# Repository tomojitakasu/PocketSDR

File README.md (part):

# **Pocket SDR - An Open-Source GNSS SDR,<br> ver. 0.22**

<div style="text-align: right;">
<strong>2026-11-03</strong>
</div>

---

## **Overview**

**Pocket SDR** is an open-source Global Navigation Satellite System (GNSS) receiver based
on software-defined radio (SDR) technology. It consists of RF frontend devices named
**Pocket SDR FE**, utilities for these devices, and GNSS SDR applications (APs) written
in Python, C, and C++. It supports almost all signals for **GPS**, **GLONASS**, **Galileo**,
**QZSS**, **BeiDou**, **NavIC**, and **SBAS**.

The Pocket SDR FE device includes 2, 4, or 8 RF frontend channels, supporting the
GNSS L1 band (1525 - 1610 MHz) or L2/L5/L6 bands (1160 - 1290 MHz). For these signal bands, refer to [**GNSS Signal Bands**](https://github.com/tomojitakasu/PocketSDR/blob/master/doc/signal_bands.pdf). Each RF channel
of the Pocket SDR FE device provides IF (intermediate-frequency) bandwidth of up to 36 MHz. The ADC sampling rate can be configured up to 32 Msps (FE 2CH) or 48 Msps (FE 4CH and FE 8CH).

Pocket SDR also includes utility programs to configure the Pocket SDR FE devices,
capture, and dump digitized IF data.
Additionally, Pocket SDR provides GNSS SDR APs to display the PSD (power spectrum density) of captured IF data, search for GNSS signals, track these signals, decode navigation data, and generate PVT (position, velocity, and time) solutions.
These utilities and APs are compatible with **Windows**, **Linux**, **Raspberry Pi OS**, **macOS**, and other environments.

The supported GNSS signals by Pocket SDR are as follows. For details on these signals and Pocket SDR signal IDs, refer to
[**GNSS Signals**](https://github.com/tomojitakasu/PocketSDR/blob/master/doc/signal_IDs.pdf).

* **GPS**: L1C/A, L1C-D, L1C-P, L2C-M, L5-I, L5-Q
* **GLONASS**: L1C/A (L1OF), L2C/A (L2OF), L1OCd, L1OCp, L2OCp, L3OCd, L3OCp
* **Galileo**: E1-B, E1-C, E5a-I, E5a-Q, E5b-I, E5b-Q, E5AltBOC (E5abQ), E6-B, E6-C
* **QZSS**: L1C/A, L1C/B, L1C-D, L1C-P, L1S, L2C-M, L5-I, L5-Q, L5S-I, L5S-Q, L6D, L6E
* **BeiDou**: B1I, B1C-D, B1C-P, B2a-D, B2a-P, B2I, B2b-I, B3I
* **NavIC**: L1-SPS-D, L1-SPS-P, L5-SPS
* **SBAS**: L1C/A, L5-I, L5-Q

These utilities and APs are written in Python, C, and C++ in a compact and modular way,
making them easy to modify for adding custom algorithms.

In addition to the Pocket SDR FE devices, Pocket SDR supports third-party
SDR hardware (**USRP**, **LimeSDR**, **bladRF**, **PlutoSDR**, **RTL-SDR**, and so on) via 
[**SoapySDR**](https://github.com/pothosware/SoapySDR/wiki).
See [**SoapySDR Device Notes**](https://github.com/tomojitakasu/PocketSDR/blob/master/doc/notes_soapy_dev.md) for verified devices,
installation notes, and device-specific caveats.

<p align="center">
  
  <b>Pocket SDR FE 2CH (v.2.0 and v.2.3), FE 4CH</b>
</p>

<p align="center">
  
  <b>Pocket SDR FE 8CH (2-RF-inputs and 8-RF-inputs)</b>
</p>

<p align="center">
  
  <b>GUI-based Real-Time GNSS SDR Receiver AP</b>
</p>

--------------------------------------------------------------------------------
<div class="pagebreak"></div>

## **Documents**

- Pocket SDR C Library API Reference
(https://github.com/tomojitakasu/PocketSDR/tree/master/doc/api_ref.pdf)

- Pocket SDR Command Reference
(https://github.com/tomojitakasu/PocketSDR/tree/master/doc/command_ref.pdf)

- Pocket SDR GNSS SDR Algorithm Description
(https://github.com/tomojitakasu/PocketSDR/tree/master/doc/algo_desc.pdf)

- Pocket SDR GNSS SDR アルゴリズム解説
(https://github.com/tomojitakasu/PocketSDR/tree/master/doc/algo_desc_jp.pdf)

- T.Takasu, An Open Source GNSS SDR: Development and Application, IPNTJ Next GNSS
Technology WG, February 21, 2022
(https://gpspp.sakura.ne.jp/paper2005/IPNTJ_NEXTWG_202202.pdf)

- T.Takasu, Development of QZSS L6 Receiver without Pilot Signal by using SDR,
IPNTJ Annual Conference, June 10, 2022
(https://gpspp.sakura.ne.jp/paper2005/IPNTJ_20220610.pdf)

- T.Takasu, Pocket SDR: Design, Implementation and Applications, A seminar for
GNSS Software Defined Receivers, Nov 19, 2024
(https://gpspp.sakura.ne.jp/paper2005/pocketsdr_seminar_202411_revA.pdf)

--------------------------------------------------------------------------------
<div class="pagebreak"></div>

## **Directory Structure and Contents**
```
PocketSDR
├── bin         # Pocket SDR APs binary programs
├── app         # Pocket SDR APs source programs
│   ├── pocket_conf  # Pocket SDR FE device configurator
│   ├── pocket_dump  # Dump digital IF data of Pocket SDR FE device
│   ├── pocket_scan  # Scan and list USB devices
│   ├── pocket_acq   # GNSS signal acquisition
│   ├── pocket_trk   # GNSS signal tracking and PVT generation
│   ├── pocket_web   # GNSS receiver server with Web UI
│   ├── pocket_snap  # Snapshot Positioning
│   ├── pocket_calib # Antenna array attitude / per-CH bias calibration
│   ├── convbin      # RINEX converter supporting Pocket SDR
│   └── str2str      # Stream converter (RTKLIB-derived)
├── src         # Pocket SDR library source programs
├── html        # Web UI files served by pocket_web (JS + CSS, no build step)
├── python      # Pocket SDR Python scripts (incl. pocket_sdr.py GUI)
├── lib         # Libraries for APs and Python scripts
│   ├── win32        # Built libraries for Windows (UCRT64)
│   ├── macos        # Built libraries for macOS
│   ├── linux        # Built libraries for Linux or Raspberry Pi OS
│   ├── build        # Makefiles to build libraries (UCRT64 / Linux / macOS)
│   ├── cyusb        # Cypress EZ-USB API (CyAPI.a) and includes
│   ├── RTKLIB       # RTKLIB source programs based on 2.4.3 b34
│   ├── pocketfft    # PocketFFT (header-only FFT, used internally)
│   └── SoapySDR     # SoapySDR headers + import lib for SDR device support
├── conf        # Configuration files for Pocket SDR FE
├── FE_2CH      # Pocket SDR FE 2CH H/W and F/W
├── FE_4CH      # Pocket SDR FE 4CH H/W and F/W
├── FE_8CH      # Pocket SDR FE 8CH H/W and F/W (3-bit RF samples)
├── driver      # Driver installation instruction for Pocket SDR FE
├── doc         # Documents (incl. api_ref.md, command_ref.md)
├── image       # Image files for documents
├── sample      # Sample digital IF data captured by Pocket SDR FE
└── test        # Test codes, scripts and data
    ├── python       # Python scripts for tests
    ├── script       # Shell scripts for tests
    ├── src          # source programs for tests
    └── utest        # makefile for unit tests

```
--------------------------------------------------------------------------------
<div class="pagebreak"></div>

## **Installation for Windows**

* Download and extract PocketSDR.zip or clone the git repository [**here**](https://github.com/tomojitakasu/PocketSDR) to an appropriate directory <install_dir>.
to an appropriate directory <install_dir>.
```
> unzip PocketSDR.zip
or
> git clone https://github.com/tomojitakasu/PocketSDR
```
* Install USB device driver for Pocket SDR FE according to [**driver/readme.txt**](https://github.com/tomojitakasu/PocketSDR/blob/master/driver/readme.txt)
.
* Install [**Python**](https://www.python.org/) with checking "Add python.exe to PATH".
* Install additional python packages as follows.
```
> pip install numpy scipy matplotlib
```
* (Optional) To use SoapySDR-supported devices (LimeSDR, HackRF, RTL-SDR,
  bladeRF, etc.), install [**radioconda**](https://github.com/ryanvolz/radioconda)
  and add `<radioconda_install_dir>\Library\bin` to PATH. See
  [SoapySDR Device Notes](https://github.com/tomojitakasu/PocketSDR/blob/master/doc/notes_soapy_dev.md#windows) for per-device
  packages, Zadig driver setup, and bladeRF version caveats.
* Add the Pocket SDR binary programs path (<install_dir>\PocketSDR\bin) to 
  the command search path (Path) of Windows environment variables.
* Add the Pocket SDR Python scripts path (<install_dir>\PocketSDR\python) to 
  the command search path (Path) of Windows environment variables.

--------------------------------------------------------------------------------

## **To rebuild binary programs for Windows**
* If you want to rebuild the binary utilities, APs, or shared libraries for the python APs
for Windows, you need [**MSYS2**](https://www.msys2.org/) with the **UCRT64** environment.
The UCRT64 toolchain links against the same C runtime (`ucrtbase.dll`) as
[**radioconda**](https://github.com/ryanvolz/radioconda)'s SoapySDR DLLs, which
gives stable high-rate streaming with SDR hardware (e.g., LimeSDR at 64 Msps).
The legacy **MINGW64** environment also builds, but suffers significant
performance loss with SoapySDR devices due to msvcrt/UCRT mixing.

* Open the **MSYS2 UCRT64** shell and install the development tools and the
  Python stack used by the python APs:
```
$ pacman -Syy
$ pacman -S git make
$ pacman -S mingw-w64-ucrt-x86_64-gcc
$ pacman -S mingw-w64-ucrt-x86_64-binutils
$ pacman -S mingw-w64-ucrt-x86_64-python
$ pacman -S mingw-w64-ucrt-x86_64-python-numpy
$ pacman -S mingw-w64-ucrt-x86_64-python-scipy
$ pacman -S mingw-w64-ucrt-x86_64-python-matplotlib
```
* If you intend to use SoapySDR-supported devices, install radioconda first.
  The default radioconda location used by the Makefiles is
  `/c/Users/<user>/radioconda/Library`. If installed elsewhere, override
  with `SOAPY_ROOT` on the make command line. See
  [SoapySDR Device Notes](https://github.com/tomojitakasu/PocketSDR/blob/master/doc/notes_soapy_dev.md#windows-build-notes)
  for details.

* If SoapySDR device support is not required, build `libsdr`, `pocket_trk`,
  and `pocket_dump` with `USE_SOAPY=0`. Pocket SDR FE USB devices and
  IF-file based processing still work; only SoapySDR device input is
  disabled. If you are rebuilding an existing tree, run `make clean` first.
```
$ cd <install_dir>/lib/build
$ make clean && make USE_SOAPY=0 && make install
$ cd <install_dir>/app/pocket_trk
$ make clean && make USE_SOAPY=0 && make install
$ cd <install_dir>/app/pocket_dump
$ make clean && make USE_SOAPY=0 && make install
```

* Move to the library build directory and build libraries.
```
$ cd <install_dir>/lib/build
$ make
$ make install
```
  The default radioconda location is `/c/Users/<user>/radioconda/Library`. If
  installed elsewhere, override on the command line:
```
$ make SOAPY_ROOT=/c/path/to/radioconda/Library
```

* Move to the application program directory and build utilities and APs.
```
$ cd <install_dir>/app
$ make
$ make install
```

* To run unit tests for the libraries:
```
$ cd <install_dir>/test/utest
$ make
$ make test
==> test_sdr_array.exe
test_sdr_array_new_free_api ... OK
test_sdr_array_ant_pos_api ... OK
t...
test_sdr_usb_req_control ... OK
```

--------------------------------------------------------------------------------
<div class="pagebreak"></div>

## **Installation for Linux or Raspberry Pi OS**

> **Note**: Pocket SDR has been verified on Ubuntu / Debian-based Linux
> distributions and on **Raspberry Pi OS (Bookworm) on Raspberry Pi 5**
> (aarch64). The Pi 5 has been confirmed to handle Pocket SDR FE and the
> apt-installed SoapySDR devices for typical L1 / L2 single-channel use;
> see the **Notes for Raspberry Pi 5** subsection below for hardware
> caveats (USB power, USB 3.0 routing, CPU limits).

* You need fundamental development packages and some libraries. Confirm the following
packages installed: git, gcc, g++, make, libusb-1.0-0-dev, libfftw3-dev, python3, python3-numpy,
python3-scipy, python3-matplotlib, python3-tk
* (Optional) To use SoapySDR-supported devices (LimeSDR, HackRF, RTL-SDR,
  SDRPlay, bladeRF, etc.), install SoapySDR and the per-device modules:
```
$ sudo apt install libsoapysdr-dev soapysdr-tools soapysdr-module-all
```
  See [SoapySDR Device Notes](https://github.com/tomojitakasu/PocketSDR/blob/master/doc/notes_soapy_dev.md#linux--raspberry-pi-os)
  for per-device package names, udev access, UHD image installation, and
  the Ubuntu 24.04 bladeRF module update workaround.

* Download and extract PocketSDR.zip or clone the git repository to an appropriate directory <install_dir>.
```
$ unzip PocketSDR.zip
or
$ git clone https://github.com/tomojitakasu/PocketSDR
```
* Move to the library build directory and build libraries.
```
$ cd <install_dir>/lib/build
$ make
$ make install
```
* Move to the application program directory and build utilities and APs.
```
$ cd <install_dir>/app
$ make
$ make install
```
* Add the Pocket SDR binary programs path (<install_dir>/PocketSDR/bin) to the command search path.

* (Recommended) Install the udev rule so the Pocket SDR FE device is
  accessible to a normal user account (no `sudo` required). The repository
  ships a ready-to-use rule at [`driver/99-pocket-sdr.rules`](https://github.com/tomojitakasu/PocketSDR/blob/master/driver/99-pocket-sdr.rules) that grants the
  `plugdev` group read/write access to Pocket SDR FE 2CH (Cypress
  EZ-USB FX2LP, VID `04B4` / PID `1004`) and FE 4CH / 8CH (Cypress
  EZ-USB FX3, VID `04B4` / PID `00F1`):
```
$ sudo cp <install_dir>/driver/99-pocket-sdr.rules /etc/udev/rules.d/
$ sudo udevadm control --reload-rules && sudo udevadm trigger
$ sudo usermod -aG plugdev $USER     # add yourself to plugdev
```
  Log out and back in (or reboot) so the new group membership takes effect,
  then unplug and re-plug the device. After that, `pocket_scan`,
  `pocket_conf`, `pocket_dump`, `pocket_trk`, and `pocket_sdr.py` all run
  without `sudo`.

  Verify the rule is in effect:
```
$ lsusb -d 04b4:                         # confirm the device is enumerated
$ ls -l /dev/bus/usb/<bus>/<dev>          # group should be "plugdev", mode 0660
$ pocket_scan                             # should list the device
```
  If your distribution uses a different group than `plugdev` (e.g.
  `dialout` on some systems, or systemd-logind's `uaccess` is sufficient
  on its own), adjust `GROUP=` in the rule file or rely on the
  `TAG+="uaccess"` line which grants access to the currently logged-in
  seat user on systemd-based systems.

* If you skip the udev rule, you must run the Pocket SDR utilities under
  `sudo` to access the USB device:
```
$ sudo pocket_conf ../conf/pocket_L1L6_12MHz.conf
$ sudo pocket_dump -t 10 ch1.bin ch2.bin
$ sudo pocket_sdr.py
```

### **Notes for Raspberry Pi 5**

Raspberry Pi 5 (Cortex-A76 4-core @ 2.4 GHz, aarch64) runs the same
build path as desktop Linux above. The Makefiles auto-detect aarch64
and enable NEON SIMD optimizations (`-DNEON`). A few Pi-specific
constraints to be aware of:

* **USB power budget**: Pi 5 advertises 5V / 5A on the official PSU but
  the USB ports share a ~1.6 A budget. USRP B210 (~2 A peak), Pocket
  SDR FE 8CH, and BladeRF 2.0 typically need either a USB Y-cable
  (separate +5V feed) or a **self-powered (externally-fed) USB hub**.
  Symptoms of insufficient power are intermittent USB resets, FPGA
  bitstream upload failures (USRP), and dropped samples.

* **USB 3.0 routing**: Pi 5 has 2× USB 3.0 + 2× USB 2.0 ports. Always
  connect high-rate SDRs (LimeSDR, USRP B210, Pocket SDR FE 8CH) to a
  USB 3.0 port. Verify enumeration speed with:
```
$ lsusb -t
```
  The relevant device should show `5000M` (USB 3.0) ? `480M` means the
  device fell back to USB 2.0, which is bandwidth-limited and will drop
  samples at high rates.

* **CPU / sample rate limits**: Pi 5 holds up well thanks to NEON SIMD
  acceleration. Measured load (`pocket_trk` realtime, single-band L1
  tracking, all-in-view PRNs):

  | Device | Sample rate × tracked channels | CPU load (of 400% = 4 cores) |
  |---|---|---|
  | LimeSDR USB | 32 Msps × 7 ch | ~280% |
  | USRP B210 | 32 Msps × 8 ch | ~290% |
  | PlutoSDR | 6 Msps × 10 ch | ~121% |
  | RTL-SDR | 2.4 Msps × 16 ch | ~102% |

  32 Msps with many tracked channels is workable but leaves limited
  headroom for additional bands or PVT processing. **8 Msps** is a
  comfortable sweet spot for general L1 use on Pi 5. Heavier configs
  (LimeSDR 60 Msps × 2-band, Pocket SDR FE 8CH × multi-band) will
  saturate the Pi 5 CPU and are intended for desktop use.

* **PocketFFT vs FFTW3**: PocketFFT (default) works on aarch64 with
  NEON. If FFT becomes a bottleneck for your workload, FFTW3 is
  marginally faster on large transforms ? install with
  `sudo apt install libfftw3-dev` and switch the build per the
  [Using FFTW3 instead of PocketFFT](#using-fftw3-instead-of-pocketfft-optional)
  section below.

* **Storage**: For long IF data captures (`pocket_dump -t <long>`,
  `pocket_trk -raw`), use a USB 3.0 SSD or NVMe HAT. The microSD card
  on stock Pi 5 cannot sustain >50 MB/s writes for extended periods
  and will drop samples.

--------------------------------------------------------------------------------
<div class="pagebreak"></div>

## **Installation for macOS**

> **Note**: Verified on Apple Silicon (arm64). Pocket SDR FE 2/4/8CH (USB)
> has been confirmed working. For SoapySDR devices on macOS, see
> [SoapySDR Device Notes](https://github.com/tomojitakasu/PocketSDR/blob/master/doc/notes_soapy_dev.md#macos).

* You need [**Homebrew**](https://brew.sh) as a base package manager. Install
  Homebrew by following the instructions on its site, then install
  development tools:
```
$ brew install libusb fftw
```

* (Optional) Install [**radioconda**](https://github.com/ryanvolz/radioconda)
  to use SoapySDR devices and a self-contained Python environment:
```
$ curl -L -O https://github.com/ryanvolz/radioconda/releases/latest/download/Radioconda-MacOSX-arm64.sh
$ bash Radioconda-MacOSX-arm64.sh
```
  For Intel mac use `Radioconda-MacOSX-x86_64.sh`. Known macOS SoapySDR
  packaging workarounds are collected in
  [SoapySDR Device Notes](https://github.com/tomojitakasu/PocketSDR/blob/master/doc/notes_soapy_dev.md#macos).

* Download and extract PocketSDR.zip or clone the git repository to an
  appropriate directory <install_dir>.
```
$ unzip PocketSDR.zip
or
$ git clone https://github.com/tomojitakasu/PocketSDR
```
* Build libraries and applications. The Makefiles auto-detect Apple
  Silicon (`Darwin arm64`) and use `clang++` for C++ sources and pull
  Homebrew's `libusb` / `fftw` headers from `/opt/homebrew/include`:
```
$ cd <install_dir>/lib/build
$ make
$ make install
$ cd <install_dir>/app
$ make
$ make install
```
* Add `<install_dir>/PocketSDR/bin` to the command search path.

* For SoapySDR-supported devices, use the driver shortcuts in
  `<install_dir>/app/pocket_trk/pocket_trk.sh`. See
  [SoapySDR Device Notes](https://github.com/tomojitakasu/PocketSDR/blob/master/doc/notes_soapy_dev.md#runtime-driver-shortcuts).

* Pocket SDR FE 2CH / 4CH / 8CH USB devices work on macOS via libusb-1.0
  with **no driver install needed** (Apple's IOUSB stack provides
  raw USB access through libusb). Plug in the device and run:
```
$ pocket_scan                                          # device should be listed
$ pocket_conf <install_dir>/conf/pocket_L1L6_12MHz.conf
$ pocket_dump -t 10 ch1.bin ch2.bin
```

--------------------------------------------------------------------------------
<div class="pagebreak"></div>

## **Using FFTW3 instead of PocketFFT (optional)**

Starting from version 0.15b, Pocket SDR ships with [**PocketFFT**](https://gitlab.mpcdf.mpg.de/mtr/pocketfft) (BSD-3-Clause) as the default FFT backend, replacing [**FFTW3**](https://www.fftw.org/) (GPL). The change is licensing-driven; for most workloads PocketFFT is competitive, but FFTW3 is still slightly faster on large transforms and supports runtime wisdom (auto-tuned plans) ? `pocket_trk` / `pocket_snap` / `pocket_acq` can read `python/fftw_wisdom.txt` for further speed-up.

To build with FFTW3 instead, install the library and build `libsdr` and the
FFT-using applications with `USE_FFTW=1`.

* Install FFTW3 (single-precision):
```
$ pacman -S mingw-w64-ucrt-x86_64-fftw    # MSYS2 UCRT64 (Windows)
$ sudo apt install libfftw3-dev           # Ubuntu / Debian / Raspberry Pi OS
$ brew install fftw                       # macOS
```
* Rebuild from scratch:
```
$ cd <install_dir>/lib/build
$ make clean && make USE_FFTW=1 && make USE_FFTW=1 install
$ cd <install_dir>/app/pocket_acq
$ make clean && make USE_FFTW=1 && make install
$ cd <install_dir>/app/pocket_snap
$ make clean && make USE_FFTW=1 && make install
$ cd <install_dir>/app/pocket_calib
$ make clean && make USE_FFTW=1 && make install
$ cd <install_dir>/app/pocket_dump
$ make clean && make USE_FFTW=1 && make install
$ cd <install_dir>/app/pocket_trk
$ make clean && make USE_FFTW=1 && make install
```
* (Optional, FFTW3 only) Generate a wisdom file tuned for the host CPU. Once present, `pocket_trk`, `pocket_snap`, and `pocket_acq` pick it up automatically.
```
$ cd <install_dir>/app/pocket_trk
$ ./fftw_wisdom -n 4096
$ cp fftw_wisdom.txt ../../python/
```

Note: FFTW3 is GPL-licensed, so a binary linked against it inherits GPL terms. Keep this in mind when redistributing.

--------------------------------------------------------------------------------
<div class="pagebreak"></div>

## **Using AVX-512 instructions (optional)**

On x86-64 CPUs with AVX-512 (AMD Zen 4 or later such as Ryzen 9000 series,
Intel Ice Lake or later), `libsdr` can be built with `USE_AVX512=1` to use the
AVX-512 versions of the carrier mixer, correlator, LPF and array covariance
kernels (`-DAVX512`) instead of the default AVX2 ones. The APs link `libsdr`
statically, so rebuild them after the library. A binary built with
`USE_AVX512=1` does not run on a CPU without AVX-512.
```
$ cd <install_dir>/lib/build
$ make clean && make USE_AVX512=1 && make install
$ cd <install_dir>/app
$ make clean && make && make install
```
The unit tests can be built with the same option: `make -C test/utest USE_AVX512=1`.

--------------------------------------------------------------------------------
<div class="pagebreak"></div>

## **GNSS SDR Utilities and APs**

Pocket SDR includes the following utilities for the Pocket SDR FE.

- **pocket_scan**: Scans and lists USB Devices.
- **pocket_conf**: Configures Pocket SDR FE device.
- **pocket_dump**: Captures and dumps IF data from the Pocket SDR FE device

Pocket SDR also provides the following GNSS SDR APs:

- **pocket_psd.py** : Plots PSD and histograms of IF data.
- **pocket_acq.py** : Performs GNSS signal acquisition from IF data.
- **pocket_trk.py** : Tracks GNSS signals and decodes navigation data in IF data.
- **pocket_snap.py**: Executes snapshot positioning using captured IF data.
- **pocket_sdr.py** : A GUI-based GNSS SDR receiver application.
- **pocket_plot.py**: Plots receiver logs generated by pocket_trk or pocket_sdr.py.
- **pocket_acq**    : A C-version of pocket_acq.py (w/o graphical plots).
- **pocket_trk**    : A C-version of pocket_trk.py (w/o graphical plots).
- **pocket_snap**   : A C-version of pocket_snap.py.
- **pocket_web**    : A GNSS SDR receiver server controlled from a Web UI.

For more details about these utilities and APs, please refer to [**Pocket SDR Command References**](https://github.com/tomojitakasu/PocketSDR/blob/master/doc/command_ref.pdf).

--------------------------------------------------------------------------------

## **GUI-based Real-Time GNSS SDR Receiver AP**

Starting from version 0.13, Pocket SDR includes a GUI-based real-time GNSS SDR
receiver AP, **pocket_sdr.py**. To execute the application, follow these steps:

```
$ chmod +x <install_dir>/python/pocket_sdr.py
$ sudo ./<install_dir>/python/pocket_sdr.py
or alternatively:
$ sudo python <install_dir>/python/pocket_sdr.py
```

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
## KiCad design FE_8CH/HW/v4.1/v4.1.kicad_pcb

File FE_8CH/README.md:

# **Pocket SDR FE 8CH - An Open-Source GNSS SDR RF Frontend**

## **Overview**

Pocket SDR FE 8H is an open-source GNSS SDR RF frontend device for Pocket SDR.
The device consists of 8 CH Maxim MAX2771 ([1]) GNSS RF front-end ICs (LNA, mixer,
filter, ADC, frequency synthesizer) and a Cypress EZ-USB FX3 USB 3.0 controller
([2], [3], [4]) to connect to host PCs. All the RF CHs are able to be configured for
GNSS L1 band (1525 - 1610 MHz), or GNSS L2/L5/L6 band (1160 - 1290 MHz).
The frequency of the reference oscillator (TCXO) is 24.000 MHz, and the ADC
sampling rate can be configured up to 48 Msps.

--------------------------------------------------------------------------------

## **Specifications**

* **Number of RF Inputs**: 8 CH or 2 CH
* **Number of RF Channels**: 8 CH
* **LO (PLL) Frequency**: 1525 ~ 1610 MHz (GNSS L1 band) or
                      1160 ~ 1290 MHz (GNSS L2/L5/L6 band)
* **IF Bandwidth**: 2.5 ~ 36 MHz
* **Sampling Rate**: 4, 6, 8, 12, 16, 24, 32 or 48 Msps
* **Sampling Type**: I-sampling 2 or 3 bits,  I/Q-sampling 2 bits
* **Host I/F**: USB 3.0 (USB 3.2 Gen1, super-speed 5Gbps), type-C
* **Power Supply**: 5V 330 mA, USB bus power

--------------------------------------------------------------------------------

## **Directory Structure and Contents**
```
FE_8CH  -+-- HW     Pocket SDR FE 8CH hardware design data
         |   |
         |   +-- v4.0     Pocket SDR FE 8CH PCB H/W data
         |   |   +-- v4.0.kicad.*     KiCAD PCB and circuit design data
         |   |   +-- v4.0.pretty      KiCAD module data
         |   |   +-- v4.0_gerber.zip  gerber data ZIP file
         |   |   +-- v4.0_gerber      gerber data
         |   |   +-- v4.0_parts.xlsx  BOM (parts list) Excel data
         |   |   +-- pocket_sdr_v2.3-eagle-import.kicad_sym  KiCAD symbol data
         |   |   +-- v4.0_case.f3d    Pocket SDR FE 8CH case Autodesk Fusion data
         |   |   +-- v4.0_case_panel_f.f3d frontpanel Autodesk Fusion data
         |   |   +-- v4.0_case_panel_b.f3d backpanel Autodesk Fusion data
         |   |   +-- ...
         |   +-- v4.1     Pocket SDR FE 8CH-2ANT PCB H/W data
         |   |   +-- ...
         |   +-- div_4px2 4PX2 RF Divider H/W data
         |       +-- ...
         +-- FW     Pocket SDR FE 8CH firmware
             +-- Packages  Cypress EZ USB Suite files
             +-- v4.0
                 +-- .metadata  Cypress EZ USB Suite files
                 +-- pocket_fw_v4
                     +-- pocket_fw_v4.c  Pocket SDR FE 8CH F/W source
                     +-- pocket_usb_dscr.c USB descriptors source
                     +-- gpif_conf.cyfx  GPIF II Designer config file 
                     +-- gpif_conf.h     GPIF II Designer generated header file
                     +-- ...
                     +-- Release
                         +-- pocket_Fw_v4.img Binary image of the F/W
                         +-- ...
```
--------------------------------------------------------------------------------

## **Rebuild F/W and Write F/W Image to Pocket SDR FE 8CH**

* Install Cypress EZ-USB FX3 Development Kit (ref [5]) to a Windows PC. As default,
it is installed to C:\Program Files (x86)\Cypress\EZ-USB FX3 SDK.
* Execute EZ USB Suite (EZ-USB FX3 SDK\1.3\Eclipse\ezUsbSuite.exe).
* Execute Menu File - Switch Workspace - Others, select <install_dir>\PocketSDR\FE_8CH\FW\v4.0
and open the workspace.
* Select pocket_fw_v4 in Project Explorer and execute Menu Project - Build All and
you can get a F/W image <install_dir>\PocketSDR\FE_8CH\FW/v4.0\pocket_fw_v4\Release\pocket_fw_v4.img.
* Disable EEPROM by connecting the J2 jumper pins on the Pocket SDR FE 8CH PCB and
attach the Pocket SDR FE 8CH via USB cable to the PC.
* Execute USB Control Center (EZ-USB FX3 SDK\1.3\bin\CyControl.exe).
* You can see "Cypress FX3 USB BootLoader Device".
* Re-enable EEPROM by disconnecting the J2 jumper pins on the Pocket SDR FE 8CH PCB.
* In USB Control Center, select "Cypress FX3 USB Bootloader Device", execute menu
Program - FX3 - I2C EEPROM, select the F/W image <install_dir>\PocketSDR\FE_8CH\FW\v4.0\pocket_fw_v4\Release\pocket_fw_v4.img
and open it.
* If you see "Programming succeeded." in status bar, the F/W is properly written
to the PocketSDR FE 8CH.

--------------------------------------------------------------------------------

## **References**

[1] Maxim integrated, MAX2771 Multiband Universal GNSS Receiver, July 2018

[2] Infineon, CYUSB301X, CYUSB201X, EZ-USB FX3 SuperSpeed USB Controller Datasheet,
Rev. Z, September 29, 2022

[3] Cypress Semiconductor, EZ-USB FX3 Technical Reference Manual, Rev.F, May 9, 2019

[4] Cypress Semiconductor, FX3 Programmers Manual, Rev.K

[5] Infineon, EZ-USB FX3 Software Development Kit
    (https://www.infineon.com/cms/jp/design-support/tools/sdk/usb-controllers-sdk/ez-usb-fx3-software-development-kit/)

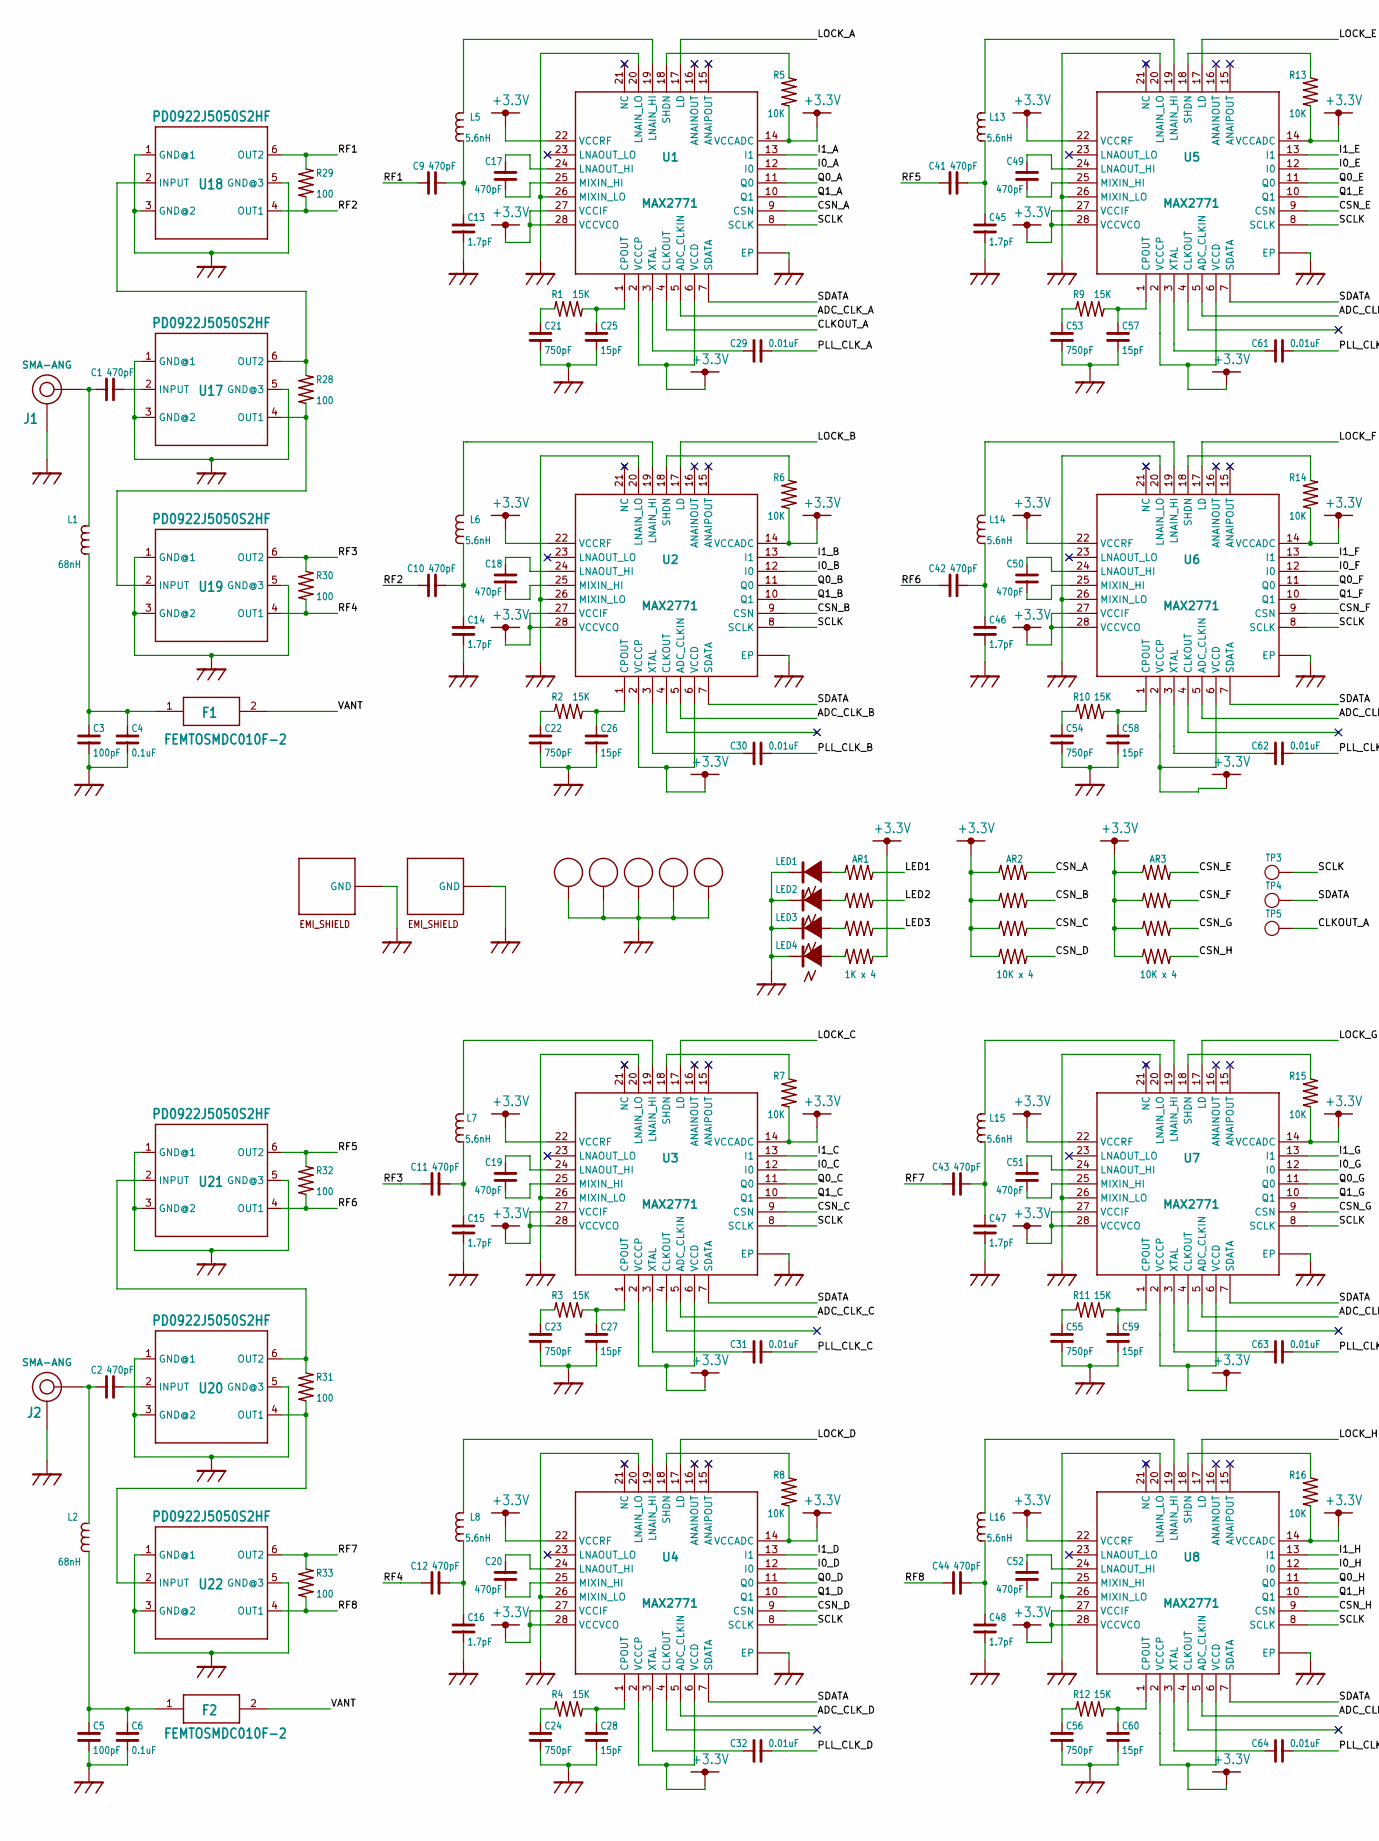
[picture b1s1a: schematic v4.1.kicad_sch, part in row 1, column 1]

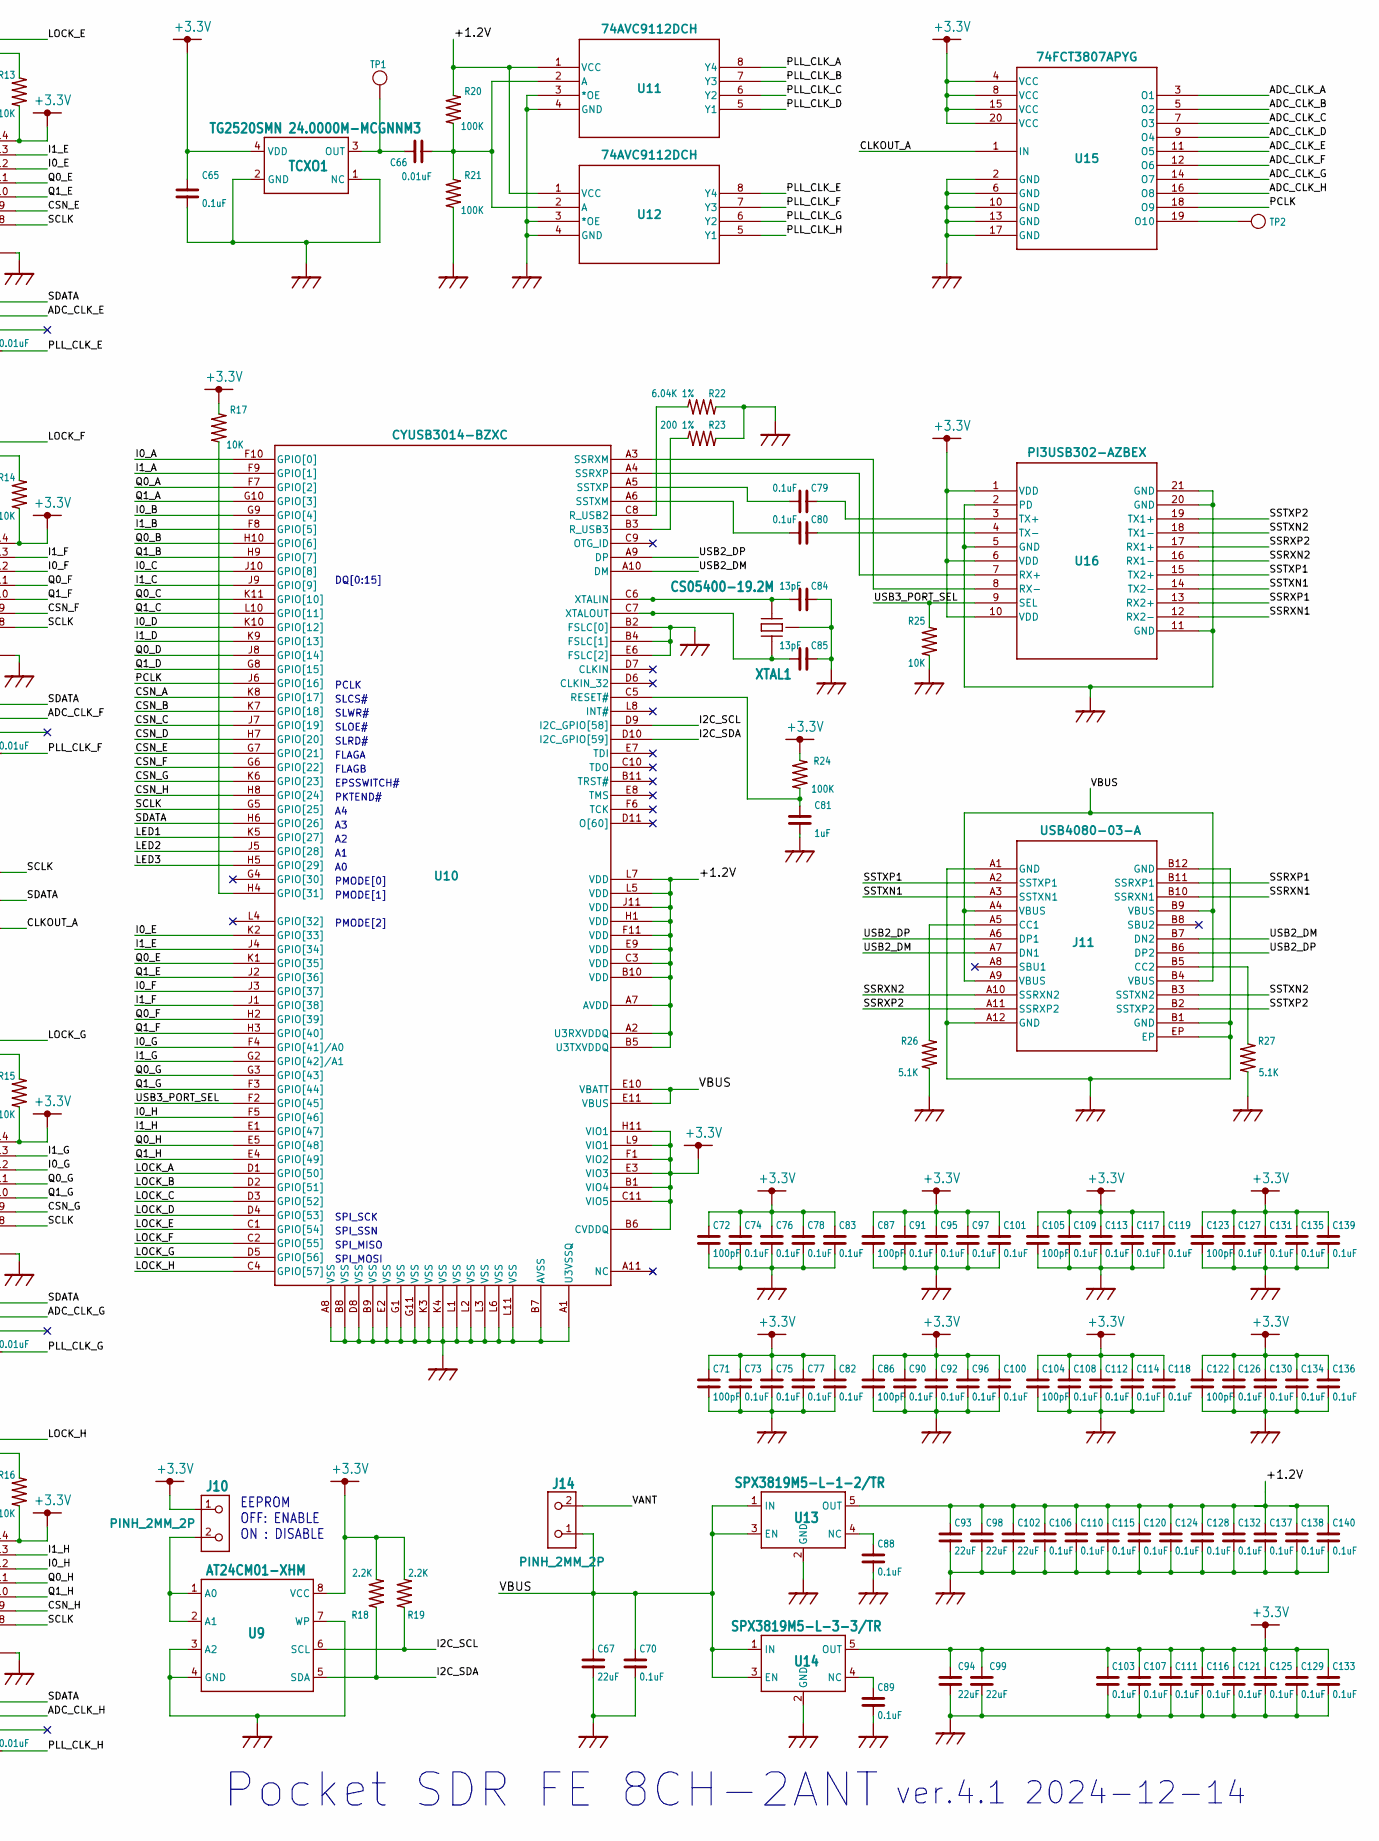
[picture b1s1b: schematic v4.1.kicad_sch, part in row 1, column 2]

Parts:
AR1: 1K x 4; EXB28V
AR2, AR3: 10K x 4; EXB28V
C1, C2, C9, C10, C11, C12, C17, C18, C19, C20, C41, C42, C43, C44, C49, C50, C51, C52: 470pF; C1005
C3, C5, C71, C72, C86, C87, C104, C105, C122, C123: 100pF; C1005
C4, C6, C65, C70, C73, C74, C75, C76, C77, C78, C79, C80, C82, C83, C88, C89, C90, C91, C92, C95, C96, C97, C100, C101, C103, C106, C107, C108, C109, C110, C111, C112, C113, C114, C115, C116, C117, C118, C119, C120, C121, C124, C125, C126, C127, C128, C129, C130, C131, C132, C133, C134, C135, C136, C137, C138, C139, C140: 0.1uF; C1005
C13, C14, C15, C16, C45, C46, C47, C48: 1.7pF; C1005
C21, C22, C23, C24, C53, C54, C55, C56: 750pF; C1005
C25, C26, C27, C28, C57, C58, C59, C60: 15pF; C1005
C29, C30, C31, C32, C61, C62, C63, C64, C66: 0.01uF; C1005
C67, C93, C94, C98, C99, C102: 22uF; C1608
C81: 1uF; C1005
C84, C85: 13pF; C1005
F1, F2: FEMTOSMDC010F-2; C1608
J1, J2: SMA-ANG
J10, J14: PINH_2MM_2P; PINH-2MM-2P
J11: USB4080-03-A; USB4080-03-A_GCT
J12, J13: MS448-10F
L1, L2: 68nH; C1608
L5, L6, L7, L8, L13, L14, L15, L16: 5.6nH; C1005
LED1, LED2, LED3, LED4: LED1608; LED_1608
PAD1, PAD2, PAD3, PAD4, PAD5: CPAD_3.2MM
R1, R2, R3, R4, R9, R10, R11, R12: 15K; C1005
R5, R6, R7, R8, R13, R14, R15, R16, R17, R25: 10K; C1005
R18, R19: 2.2K; C1005
R20, R21, R24: 100K; C1005
R22: 6.04K 1%; C1005
R23: 200 1%; C1005
R26, R27: 5.1K; C1005
R28, R29, R30, R31, R32, R33: 100; C1005
TCXO1: TG2520SMN 24.0000M-MCGNNM3; TCXO
TP1, TP2, TP3, TP4, TP5: TP0.5
U1, U2, U3, U4, U5, U6, U7, U8: MAX2771; TQFN28
U9: AT24CM01-XHM; TSSOP_8P
U10: CYUSB3014-BZXC; BGA-121
U11, U12: 74AVC9112DCH; VSSOP8_SOT765-1_NEX
U13: SPX3819M5-L-1-2/TR; SOT23
U14: SPX3819M5-L-3-3/TR; SOT23
U15: 74FCT3807APYG; SSOP20
U16: PI3USB302-AZBEX; 20TQFN-ZB_PI3USB302-A_DIO
U17, U18, U19, U20, U21, U22: PD0922J5050S2HF; RF_DIV
XTAL1: CS05400-19.2M; XTAL_SMD

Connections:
+3.3V: AR1.8, AR2.1, AR2.3, AR2.5, AR2.7, AR3.1, AR3.3, AR3.5, AR3.7, C65.1, C71.1, C72.1, C73.1, C74.1, C75.1, C76.1, C77.1, C78.1, C82.1, C83.1, C86.1, C87.1, C90.1, C91.1, C92.1, C94.1, C95.1, C96.1, C97.1, C99.1, C100.1, C101.1, C103.1, C104.1, C105.1, C107.1, C108.1, C109.1, C111.1, C112.1, C113.1, C114.1, C116.1, C117.1, C118.1, C119.1, C121.1, C122.1, C123.1, C125.1, C126.1, C127.1, C129.1, C130.1, C131.1, C133.1, C134.1, C135.1, C136.1, C139.1, J10.1, R5.1, R6.1, R7.1, R8.1, R13.1, R14.1, R15.1, R16.1, R17.1, R18.2, R19.2, R24.2, TCXO1.4 (VDD), U1.2 (VCCCP), U1.6 (VCCD), U1.14 (VCCADC), U1.22 (VCCRF), U1.27 (VCCIF), U1.28 (VCCVCO), U2.2 (VCCCP), U2.6 (VCCD), U2.14 (VCCADC), U2.22 (VCCRF), U2.27 (VCCIF), U2.28 (VCCVCO), U3.2 (VCCCP), U3.6 (VCCD), U3.14 (VCCADC), U3.22 (VCCRF), U3.27 (VCCIF), U3.28 (VCCVCO), U4.2 (VCCCP), U4.6 (VCCD), U4.14 (VCCADC), U4.22 (VCCRF), U4.27 (VCCIF), U4.28 (VCCVCO), U5.2 (VCCCP), U5.6 (VCCD), U5.14 (VCCADC), U5.22 (VCCRF), U5.27 (VCCIF), U5.28 (VCCVCO), U6.2 (VCCCP), U6.6 (VCCD), U6.14 (VCCADC), U6.22 (VCCRF), U6.27 (VCCIF), U6.28 (VCCVCO), U7.2 (VCCCP), U7.6 (VCCD), U7.14 (VCCADC), U7.22 (VCCRF), U7.27 (VCCIF), U7.28 (VCCVCO), U8.2 (VCCCP), U8.6 (VCCD), U8.14 (VCCADC), U8.22 (VCCRF), U8.27 (VCCIF), U8.28 (VCCVCO), U9.8 (VCC), U10.B1 (VIO4), U10.B6 (CVDDQ), U10.C11 (VIO5), U10.E3 (VIO3), U10.F1 (VIO2), U10.H11 (VIO1), U10.L9 (VIO1), U14.5 (OUT), U15.4 (VCC), U15.8 (VCC), U15.15 (VCC), U15.20 (VCC), U16.1 (VDD), U16.6 (VDD), U16.10 (VDD)
/+1.2V: C93.1, C98.1, C102.1, C106.1, C110.1, C115.1, C120.1, C124.1, C128.1, C132.1, C137.1, C138.1, C140.1, R20.1, U10.A2 (U3RXVDDQ), U10.A7 (AVDD), U10.B5 (U3TXVDDQ), U10.B10 (VDD), U10.C3 (VDD), U10.E9 (VDD), U10.F11 (VDD), U10.H1 (VDD), U10.J11 (VDD), U10.L5 (VDD), U10.L7 (VDD), U11.1 (VCC), U12.1 (VCC), U13.5 (OUT)
/ADC_CLK_A: U1.5 (ADC_CLKIN), U15.3 (O1)
/ADC_CLK_B: U2.5 (ADC_CLKIN), U15.5 (O2)
/ADC_CLK_C: U3.5 (ADC_CLKIN), U15.7 (O3)
/ADC_CLK_D: U4.5 (ADC_CLKIN), U15.9 (O4)
/ADC_CLK_E: U5.5 (ADC_CLKIN), U15.11 (O5)
/ADC_CLK_F: U6.5 (ADC_CLKIN), U15.12 (O6)
/ADC_CLK_G: U7.5 (ADC_CLKIN), U15.14 (O7)
/ADC_CLK_H: U8.5 (ADC_CLKIN), U15.16 (O8)
/CLKOUT_A: TP5.1, U1.4 (CLKOUT), U15.1 (IN)
/CSN_A: AR2.2, U1.9 (CSN), U10.K8 (GPIO[17])
/CSN_B: AR2.4, U2.9 (CSN), U10.K7 (GPIO[18])
/CSN_C: AR2.6, U3.9 (CSN), U10.J7 (GPIO[19])
/CSN_D: AR2.8, U4.9 (CSN), U10.H7 (GPIO[20])
/CSN_E: AR3.2, U5.9 (CSN), U10.G7 (GPIO[21])
/CSN_F: AR3.4, U6.9 (CSN), U10.G6 (GPIO[22])
/CSN_G: AR3.6, U7.9 (CSN), U10.K6 (GPIO[23])
/CSN_H: AR3.8, U8.9 (CSN), U10.H8 (GPIO[24])
/I0_A: U1.12 (I0), U10.F10 (GPIO[0])
/I0_B: U2.12 (I0), U10.G9 (GPIO[4])
/I0_C: U3.12 (I0), U10.J10 (GPIO[8])
/I0_D: U4.12 (I0), U10.K10 (GPIO[12])
/I0_E: U5.12 (I0), U10.K2 (GPIO[33])
/I0_F: U6.12 (I0), U10.J3 (GPIO[37])
/I0_G: U7.12 (I0), U10.F4 (GPIO[41]/A0)
/I0_H: U8.12 (I0), U10.F5 (GPIO[46])
/I1_A: U1.13 (I1), U10.F9 (GPIO[1])
/I1_B: U2.13 (I1), U10.F8 (GPIO[5])
/I1_C: U3.13 (I1), U10.J9 (GPIO[9])
/I1_D: U4.13 (I1), U10.K9 (GPIO[13])
/I1_E: U5.13 (I1), U10.J4 (GPIO[34])
/I1_F: U6.13 (I1), U10.J1 (GPIO[38])
/I1_G: U7.13 (I1), U10.G2 (GPIO[42]/A1)
/I1_H: U8.13 (I1), U10.E1 (GPIO[47])
/I2C_SCL: R19.1, U9.6 (SCL), U10.D9 (I2C_GPIO[58])
/I2C_SDA: R18.1, U9.5 (SDA), U10.D10 (I2C_GPIO[59])
/LED1: AR1.2, U10.K5 (GPIO[27])
/LED2: AR1.4, U10.J5 (GPIO[28])
/LED3: AR1.6, U10.H5 (GPIO[29])
/LOCK_A: U1.17 (LD), U10.D1 (GPIO[50])
/LOCK_B: U2.17 (LD), U10.D2 (GPIO[51])
/LOCK_C: U3.17 (LD), U10.D3 (GPIO[52])
/LOCK_D: U4.17 (LD), U10.D4 (GPIO[53])
/LOCK_E: U5.17 (LD), U10.C1 (GPIO[54])
/LOCK_F: U6.17 (LD), U10.C2 (GPIO[55])
/LOCK_G: U7.17 (LD), U10.D5 (GPIO[56])
/LOCK_H: U8.17 (LD), U10.C4 (GPIO[57])
/PCLK: U10.J6 (GPIO[16]), U15.18 (O9)
/PLL_CLK_A: C29.1, U11.8 (Y4)
/PLL_CLK_B: C30.1, U11.7 (Y3)
/PLL_CLK_C: C31.1, U11.6 (Y2)
/PLL_CLK_D: C32.1, U11.5 (Y1)
/PLL_CLK_E: C61.1, U12.8 (Y4)
/PLL_CLK_F: C62.1, U12.7 (Y3)
/PLL_CLK_G: C63.1, U12.6 (Y2)
/PLL_CLK_H: C64.1, U12.5 (Y1)
/Q0_A: U1.11 (Q0), U10.F7 (GPIO[2])
/Q0_B: U2.11 (Q0), U10.H10 (GPIO[6])
/Q0_C: U3.11 (Q0), U10.K11 (GPIO[10])
/Q0_D: U4.11 (Q0), U10.J8 (GPIO[14])
/Q0_E: U5.11 (Q0), U10.K1 (GPIO[35])
/Q0_F: U6.11 (Q0), U10.H2 (GPIO[39])
/Q0_G: U7.11 (Q0), U10.G3 (GPIO[43])
/Q0_H: U8.11 (Q0), U10.E5 (GPIO[48])
/Q1_A: U1.10 (Q1), U10.G10 (GPIO[3])
/Q1_B: U2.10 (Q1), U10.H9 (GPIO[7])
/Q1_C: U3.10 (Q1), U10.L10 (GPIO[11])
/Q1_D: U4.10 (Q1), U10.G8 (GPIO[15])
/Q1_E: U5.10 (Q1), U10.J2 (GPIO[36])
/Q1_F: U6.10 (Q1), U10.H3 (GPIO[40])
/Q1_G: U7.10 (Q1), U10.F3 (GPIO[44])
/Q1_H: U8.10 (Q1), U10.E4 (GPIO[49])
/RF1: C9.1, R29.2, U18.6 (OUT2)
/RF2: C10.1, R29.1, U18.4 (OUT1)
/RF3: C11.1, R30.2, U19.6 (OUT2)
/RF4: C12.1, R30.1, U19.4 (OUT1)
/RF5: C41.1, R32.2, U21.6 (OUT2)
/RF6: C42.1, R32.1, U21.4 (OUT1)
/RF7: C43.1, R33.2, U22.6 (OUT2)
/RF8: C44.1, R33.1, U22.4 (OUT1)
/SCLK: TP3.1, U1.8 (SCLK), U2.8 (SCLK), U3.8 (SCLK), U4.8 (SCLK), U5.8 (SCLK), U6.8 (SCLK), U7.8 (SCLK), U8.8 (SCLK), U10.G5 (GPIO[25])
/SDATA: TP4.1, U1.7 (SDATA), U2.7 (SDATA), U3.7 (SDATA), U4.7 (SDATA), U5.7 (SDATA), U6.7 (SDATA), U7.7 (SDATA), U8.7 (SDATA), U10.H6 (GPIO[26])
/SSRXN1: J11.B10 (SSRXN1), U16.12 (RX2-)
/SSRXN2: J11.A10 (SSRXN2), U16.16 (RX1-)
/SSRXP1: J11.B11 (SSRXP1), U16.13 (RX2+)
/SSRXP2: J11.A11 (SSRXP2), U16.17 (RX1+)
/SSTXN1: J11.A3 (SSTXN1), U16.14 (TX2-)
/SSTXN2: J11.B3 (SSTXN2), U16.18 (TX1-)
/SSTXP1: J11.A2 (SSTXP1), U16.15 (TX2+)
/SSTXP2: J11.B2 (SSTXP2), U16.19 (TX1+)
/USB2_DM: J11.A7 (DN1), J11.B7 (DN2), U10.A10 (DM)
/USB2_DP: J11.A6 (DP1), J11.B6 (DP2), U10.A9 (DP)
/USB3_PORT_SEL: R25.2, U10.F2 (GPIO[45]), U16.9 (SEL)
/VANT: F1.2, F2.2, J14.2
/VBUS: C67.1, C70.1, J11.A4 (VBUS), J11.A9 (VBUS), J11.B4 (VBUS), J11.B9 (VBUS), J14.1, U10.E10 (VBATT), U10.E11 (VBUS), U13.1 (IN), U13.3 (EN), U14.1 (IN), U14.3 (EN)
GND: C3.2, C4.2, C5.2, C6.2, C13.1, C14.1, C15.1, C16.1, C21.2, C22.2, C23.2, C24.2, C25.2, C26.2, C27.2, C28.2, C45.1, C46.1, C47.1, C48.1, C53.2, C54.2, C55.2, C56.2, C57.2, C58.2, C59.2, C60.2, C65.2, C67.2, C70.2, C71.2, C72.2, C73.2, C74.2, C75.2, C76.2, C77.2, C78.2, C81.2, C82.2, C83.2, C84.1, C85.1, C86.2, C87.2, C88.2, C89.2, C90.2, C91.2, C92.2, C93.2, C94.2, C95.2, C96.2, C97.2, C98.2, C99.2, C100.2, C101.2, C102.2, C103.2, C104.2, C105.2, C106.2, C107.2, C108.2, C109.2, C110.2, C111.2, C112.2, C113.2, C114.2, C115.2, C116.2, C117.2, C118.2, C119.2, C120.2, C121.2, C122.2, C123.2, C124.2, C125.2, C126.2, C127.2, C128.2, C129.2, C130.2, C131.2, C132.2, C133.2, C134.2, C135.2, C136.2, C137.2, C138.2, C139.2, C140.2, J1.P2 (GND), J1.P3 (GND), J1.P4 (GND), J1.P5 (GND), J2.P2 (GND), J2.P3 (GND), J2.P4 (GND), J2.P5 (GND), J11.A1 (GND), J11.A12 (GND), J11.B1 (GND), J11.B12 (GND), J11.EP, J12.P (GND), J13.P (GND), LED1.2, LED2.2, LED3.2, LED4.2, PAD1.EP, PAD2.EP, PAD3.EP, PAD4.EP, PAD5.EP, R21.2, R22.1, R23.1, R25.1, R26.1, R27.1, TCXO1.1 (NC), TCXO1.2 (GND), U1.20 (LNAIN_LO), U1.26 (MIXIN_LO), U1.C1 (EP), U1.C2 (EP), U1.C3 (EP), U1.C4 (EP), U1.EP, U1.V1 (EP), U1.V2 (EP), U1.V3 (EP), U1.V4 (EP), U1.V5 (EP), U1.V6 (EP), U1.V7 (EP), U1.V8 (EP), U1.V9 (EP), U2.20 (LNAIN_LO), U2.26 (MIXIN_LO), U2.C1 (EP), U2.C2 (EP), U2.C3 (EP), U2.C4 (EP), U2.EP, U2.V1 (EP), U2.V2 (EP), U2.V3 (EP), U2.V4 (EP), U2.V5 (EP), U2.V6 (EP), U2.V7 (EP), U2.V8 (EP), U2.V9 (EP), U3.20 (LNAIN_LO), U3.26 (MIXIN_LO), U3.C1 (EP), U3.C2 (EP), U3.C3 (EP), U3.C4 (EP), U3.EP, U3.V1 (EP), U3.V2 (EP), U3.V3 (EP), U3.V4 (EP), U3.V5 (EP), U3.V6 (EP), U3.V7 (EP), U3.V8 (EP), U3.V9 (EP), U4.20 (LNAIN_LO), U4.26 (MIXIN_LO), U4.C1 (EP), U4.C2 (EP), U4.C3 (EP), U4.C4 (EP), U4.EP, U4.V1 (EP), U4.V2 (EP), U4.V3 (EP), U4.V4 (EP), U4.V5 (EP), U4.V6 (EP), U4.V7 (EP), U4.V8 (EP), U4.V9 (EP), U5.20 (LNAIN_LO), U5.26 (MIXIN_LO), U5.C1 (EP), U5.C2 (EP), U5.C3 (EP), U5.C4 (EP), U5.EP, U5.V1 (EP), U5.V2 (EP), U5.V3 (EP), U5.V4 (EP), U5.V5 (EP), U5.V6 (EP), U5.V7 (EP), U5.V8 (EP), U5.V9 (EP), U6.20 (LNAIN_LO), U6.26 (MIXIN_LO), U6.C1 (EP), U6.C2 (EP), U6.C3 (EP), U6.C4 (EP), U6.EP, U6.V1 (EP), U6.V2 (EP), U6.V3 (EP), U6.V4 (EP), U6.V5 (EP), U6.V6 (EP), U6.V7 (EP), U6.V8 (EP), U6.V9 (EP), U7.20 (LNAIN_LO), U7.26 (MIXIN_LO), U7.C1 (EP), U7.C2 (EP), U7.C3 (EP), U7.C4 (EP), U7.EP, U7.V1 (EP), U7.V2 (EP), U7.V3 (EP), U7.V4 (EP), U7.V5 (EP), U7.V6 (EP), U7.V7 (EP), U7.V8 (EP), U7.V9 (EP), U8.20 (LNAIN_LO), U8.26 (MIXIN_LO), U8.C1 (EP), U8.C2 (EP), U8.C3 (EP), U8.C4 (EP), U8.EP, U8.V1 (EP), U8.V2 (EP), U8.V3 (EP), U8.V4 (EP), U8.V5 (EP), U8.V6 (EP), U8.V7 (EP), U8.V8 (EP), U8.V9 (EP), U9.3 (A2), U9.4 (GND), U9.7 (WP), U10.A1 (U3VSSQ), U10.A8 (VSS), U10.B2 (FSLC[0]), U10.B4 (FSLC[1]), U10.B7 (AVSS), U10.B8 (VSS), U10.B9 (VSS), U10.D8 (VSS), U10.E2 (VSS), U10.E6 (FSLC[2]), U10.G1 (VSS), U10.G11 (VSS), U10.K3 (VSS), U10.K4 (VSS), U10.L1 (VSS), U10.L2 (VSS), U10.L3 (VSS), U10.L6 (VSS), U10.L11 (VSS), U11.3 (*OE), U11.4 (GND), U12.3 (*OE), U12.4 (GND), U13.2 (GND), U14.2 (GND), U15.2 (GND), U15.6 (GND), U15.10 (GND), U15.13 (GND), U15.17 (GND), U16.2 (PD), U16.5 (GND), U16.11 (GND), U16.20 (GND), U16.21 (GND), U17.1 (GND@1), U17.3 (GND@2), U17.5 (GND@3), U18.1 (GND@1), U18.3 (GND@2), U18.5 (GND@3), U19.1 (GND@1), U19.3 (GND@2), U19.5 (GND@3), U20.1 (GND@1), U20.3 (GND@2), U20.5 (GND@3), U21.1 (GND@1), U21.3 (GND@2), U21.5 (GND@3), U22.1 (GND@1), U22.3 (GND@2), U22.5 (GND@3), XTAL1.P2 (GND), XTAL1.P4 (GND)
unnamed: AR1.1, LED1.1 (+)
unnamed: AR1.3, LED2.1 (+)
unnamed: AR1.5, LED3.1 (+)
unnamed: AR1.7, LED4.1 (+)
unnamed: C3.1, C4.1, F1.1, L1.1
unnamed: C5.1, C6.1, F2.1, L2.1
unnamed: C1.1, J1.P1 (RF), L1.2
unnamed: C2.1, J2.P1 (RF), L2.2
unnamed: J10.2, U9.1 (A0), U9.2 (A1)
unnamed: J11.A5 (CC1), R26.2
unnamed: J11.B5 (CC2), R27.2
unnamed: C9.2, C13.2, L5.1
unnamed: L5.2, U1.19 (LNAIN_HI)
unnamed: C10.2, C14.2, L6.1
unnamed: L6.2, U2.19 (LNAIN_HI)
unnamed: C11.2, C15.2, L7.1
unnamed: L7.2, U3.19 (LNAIN_HI)
unnamed: C12.2, C16.2, L8.1
unnamed: L8.2, U4.19 (LNAIN_HI)
unnamed: C41.2, C45.2, L13.1
unnamed: L13.2, U5.19 (LNAIN_HI)
unnamed: C42.2, C46.2, L14.1
unnamed: L14.2, U6.19 (LNAIN_HI)
unnamed: C43.2, C47.2, L15.1
unnamed: L15.2, U7.19 (LNAIN_HI)
unnamed: C44.2, C48.2, L16.1
unnamed: L16.2, U8.19 (LNAIN_HI)
unnamed: C21.1, R1.1
unnamed: C25.1, R1.2, U1.1 (CPOUT)
unnamed: C22.1, R2.1
unnamed: C26.1, R2.2, U2.1 (CPOUT)
unnamed: C23.1, R3.1
unnamed: C27.1, R3.2, U3.1 (CPOUT)
unnamed: C24.1, R4.1
unnamed: C28.1, R4.2, U4.1 (CPOUT)
unnamed: R5.2, U1.18 (SHDN)
unnamed: R6.2, U2.18 (SHDN)
unnamed: R7.2, U3.18 (SHDN)
unnamed: R8.2, U4.18 (SHDN)
unnamed: C53.1, R9.1
unnamed: C57.1, R9.2, U5.1 (CPOUT)
unnamed: C54.1, R10.1
unnamed: C58.1, R10.2, U6.1 (CPOUT)
unnamed: C55.1, R11.1
unnamed: C59.1, R11.2, U7.1 (CPOUT)
unnamed: C56.1, R12.1
unnamed: C60.1, R12.2, U8.1 (CPOUT)
unnamed: R13.2, U5.18 (SHDN)
unnamed: R14.2, U6.18 (SHDN)
unnamed: R15.2, U7.18 (SHDN)
unnamed: R16.2, U8.18 (SHDN)
unnamed: R17.2, U10.H4 (GPIO[31])
unnamed: C66.2, R20.2, R21.1, U11.2 (A), U12.2 (A)
unnamed: R22.2, U10.C8 (R_USB2)
unnamed: R23.2, U10.B3 (R_USB3)
unnamed: C81.1, R24.1, U10.C5 (RESET#)
unnamed: R28.1, U17.4 (OUT1), U19.2 (INPUT)
unnamed: R28.2, U17.6 (OUT2), U18.2 (INPUT)
unnamed: R31.1, U20.4 (OUT1), U22.2 (INPUT)
unnamed: R31.2, U20.6 (OUT2), U21.2 (INPUT)
unnamed: C66.1, TCXO1.3 (OUT), TP1.1
unnamed: C17.1, U1.24 (LNAOUT_HI)
unnamed: C17.2, U1.25 (MIXIN_HI)
unnamed: C29.2, U1.3 (XTAL)
unnamed: C18.1, U2.24 (LNAOUT_HI)
unnamed: C18.2, U2.25 (MIXIN_HI)
unnamed: C30.2, U2.3 (XTAL)
unnamed: C19.1, U3.24 (LNAOUT_HI)
unnamed: C19.2, U3.25 (MIXIN_HI)
unnamed: C31.2, U3.3 (XTAL)
unnamed: C20.1, U4.24 (LNAOUT_HI)
unnamed: C20.2, U4.25 (MIXIN_HI)
unnamed: C32.2, U4.3 (XTAL)
unnamed: C49.1, U5.24 (LNAOUT_HI)
unnamed: C49.2, U5.25 (MIXIN_HI)
unnamed: C61.2, U5.3 (XTAL)
unnamed: C50.1, U6.24 (LNAOUT_HI)
unnamed: C50.2, U6.25 (MIXIN_HI)
unnamed: C62.2, U6.3 (XTAL)
unnamed: C51.1, U7.24 (LNAOUT_HI)
unnamed: C51.2, U7.25 (MIXIN_HI)
unnamed: C63.2, U7.3 (XTAL)
unnamed: C52.1, U8.24 (LNAOUT_HI)
unnamed: C52.2, U8.25 (MIXIN_HI)
unnamed: C64.2, U8.3 (XTAL)
unnamed: U10.A3 (SSRXM), U16.8 (RX-)
unnamed: U10.A4 (SSRXP), U16.7 (RX+)
unnamed: C80.2, U10.A6 (SSTXM)
unnamed: C79.2, U10.A5 (SSTXP)
unnamed: C84.2, U10.C6 (XTALIN), XTAL1.P1 (XTAL1)
unnamed: C85.2, U10.C7 (XTALOUT), XTAL1.P3 (XTAL2)
unnamed: C88.1, U13.4 (NC)
unnamed: C89.1, U14.4 (NC)
unnamed: TP2.1, U15.19 (O10)
unnamed: C79.1, U16.3 (TX+)
unnamed: C80.1, U16.4 (TX-)
unnamed: C1.2, U17.2 (INPUT)
unnamed: C2.2, U20.2 (INPUT)

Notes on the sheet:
PCLK
EPSSWITCH#
SPI_SSN
PMODE[1]
DQ[0:15]
Pocket SDR FE 8CH-2ANT
PMODE[0]
EEPROM OFF: ENABLE ON : DISABLE
SPI_SCK
SPI_MOSI
SLRD#
SLOE#
SLCS#
PMODE[2]
SLWR#
PKTEND#
ver.4.1 2024-12-14
SPI_MISO
FLAGA
FLAGB
